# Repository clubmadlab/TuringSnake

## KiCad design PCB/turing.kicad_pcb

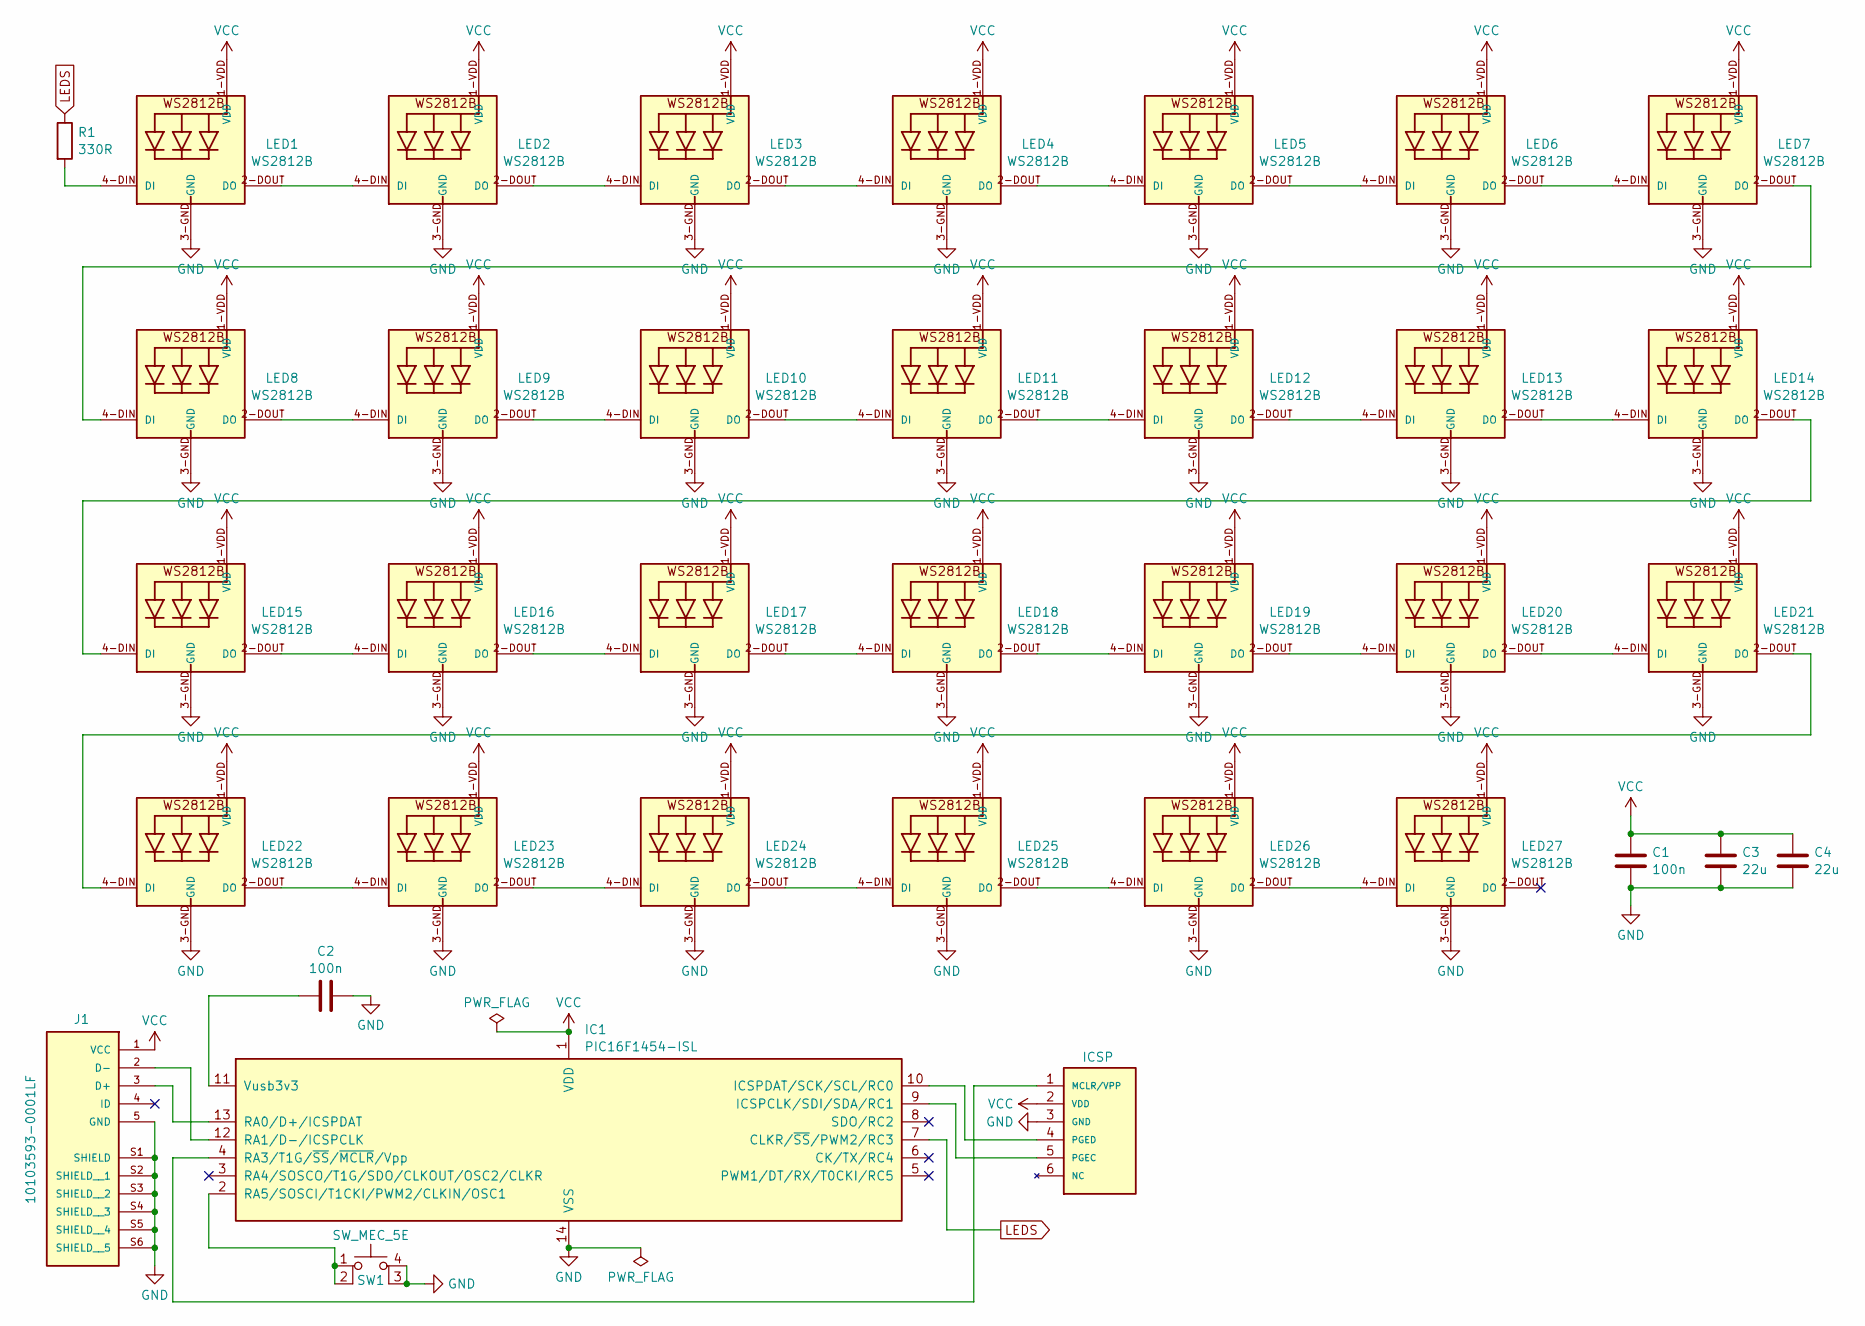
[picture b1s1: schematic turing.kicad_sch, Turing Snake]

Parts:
C1, C2: 100n; C_1206
C3, C4: 22u; C_1206
IC1: PIC16F1454-ISL; SOIC14
ICSP1: ICSP
J1: 10103593-0001LF; AMPHENOL_10103593-0001LF
LED1, LED2, LED3, LED4, LED5, LED6, LED7, LED8, LED9, LED10, LED11, LED12, LED13, LED14, LED15, LED16, LED17, LED18, LED19, LED20, LED21, LED22, LED23, LED24, LED25, LED26, LED27: WS2812B
R1: 330R; R_1206
SW1: SW_MEC_5E; pushbutton_min_tactile_SMD

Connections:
GND: C1.2, C2.1, C3.2, C4.2, IC1.14 (VSS), ICSP1.3 (GND), J1.5 (GND), J1.S1 (SHIELD), J1.S2 (SHIELD__1), J1.S3 (SHIELD__2), J1.S4 (SHIELD__3), J1.S5 (SHIELD__4), J1.S6 (SHIELD__5), LED1.3-GND (GND), LED2.3-GND (GND), LED3.3-GND (GND), LED4.3-GND (GND), LED5.3-GND (GND), LED6.3-GND (GND), LED7.3-GND (GND), LED8.3-GND (GND), LED9.3-GND (GND), LED10.3-GND (GND), LED11.3-GND (GND), LED12.3-GND (GND), LED13.3-GND (GND), LED14.3-GND (GND), LED15.3-GND (GND), LED16.3-GND (GND), LED17.3-GND (GND), LED18.3-GND (GND), LED19.3-GND (GND), LED20.3-GND (GND), LED21.3-GND (GND), LED22.3-GND (GND), LED23.3-GND (GND), LED24.3-GND (GND), LED25.3-GND (GND), LED26.3-GND (GND), LED27.3-GND (GND), SW1.3 (K), SW1.4 (A)
LEDS: IC1.7 (CLKR/~SS/PWM2/RC3), R1.1
unnamed: IC1.9 (ICSPCLK/SDI/SDA/RC1), ICSP1.5 (PGEC)
unnamed: IC1.10 (ICSPDAT/SCK/SCL/RC0), ICSP1.4 (PGED)
unnamed: IC1.13 (RA0/D+/ICSPDAT), J1.3 (D+)
unnamed: IC1.12 (RA1/D-/ICSPCLK), J1.2 (D-)
unnamed: IC1.4 (RA3/T1G/~SS/~MCLR/Vpp), ICSP1.1 (MCLR/VPP)
unnamed: IC1.2 (RA5/SOSCI/T1CKI/PWM2/CLKIN/OSC1), SW1.1, SW1.2
unnamed: C2.2, IC1.11 (Vusb3v3)
unnamed: LED1.4-DIN (DI), R1.2
unnamed: LED1.2-DOUT (DO), LED2.4-DIN (DI)
unnamed: LED2.2-DOUT (DO), LED3.4-DIN (DI)
unnamed: LED3.2-DOUT (DO), LED4.4-DIN (DI)
unnamed: LED4.2-DOUT (DO), LED5.4-DIN (DI)
unnamed: LED5.2-DOUT (DO), LED6.4-DIN (DI)
unnamed: LED6.2-DOUT (DO), LED7.4-DIN (DI)
unnamed: LED7.2-DOUT (DO), LED8.4-DIN (DI)
unnamed: LED8.2-DOUT (DO), LED9.4-DIN (DI)
unnamed: LED9.2-DOUT (DO), LED10.4-DIN (DI)
unnamed: LED10.2-DOUT (DO), LED11.4-DIN (DI)
unnamed: LED11.2-DOUT (DO), LED12.4-DIN (DI)
unnamed: LED12.2-DOUT (DO), LED13.4-DIN (DI)
unnamed: LED13.2-DOUT (DO), LED14.4-DIN (DI)
unnamed: LED14.2-DOUT (DO), LED15.4-DIN (DI)
unnamed: LED15.2-DOUT (DO), LED16.4-DIN (DI)
unnamed: LED16.2-DOUT (DO), LED17.4-DIN (DI)
unnamed: LED17.2-DOUT (DO), LED18.4-DIN (DI)
unnamed: LED18.2-DOUT (DO), LED19.4-DIN (DI)
unnamed: LED19.2-DOUT (DO), LED20.4-DIN (DI)
unnamed: LED20.2-DOUT (DO), LED21.4-DIN (DI)
unnamed: LED21.2-DOUT (DO), LED22.4-DIN (DI)
unnamed: LED22.2-DOUT (DO), LED23.4-DIN (DI)
unnamed: LED23.2-DOUT (DO), LED24.4-DIN (DI)
unnamed: LED24.2-DOUT (DO), LED25.4-DIN (DI)
unnamed: LED25.2-DOUT (DO), LED26.4-DIN (DI)
unnamed: LED26.2-DOUT (DO), LED27.4-DIN (DI)
VCC: C1.1, C3.1, C4.1, IC1.1 (VDD), ICSP1.2 (VDD), J1.1 (VCC), LED1.1-VDD (VDD), LED2.1-VDD (VDD), LED3.1-VDD (VDD), LED4.1-VDD (VDD), LED5.1-VDD (VDD), LED6.1-VDD (VDD), LED7.1-VDD (VDD), LED8.1-VDD (VDD), LED9.1-VDD (VDD), LED10.1-VDD (VDD), LED11.1-VDD (VDD), LED12.1-VDD (VDD), LED13.1-VDD (VDD), LED14.1-VDD (VDD), LED15.1-VDD (VDD), LED16.1-VDD (VDD), LED17.1-VDD (VDD), LED18.1-VDD (VDD), LED19.1-VDD (VDD), LED20.1-VDD (VDD), LED21.1-VDD (VDD), LED22.1-VDD (VDD), LED23.1-VDD (VDD), LED24.1-VDD (VDD), LED25.1-VDD (VDD), LED26.1-VDD (VDD), LED27.1-VDD (VDD)

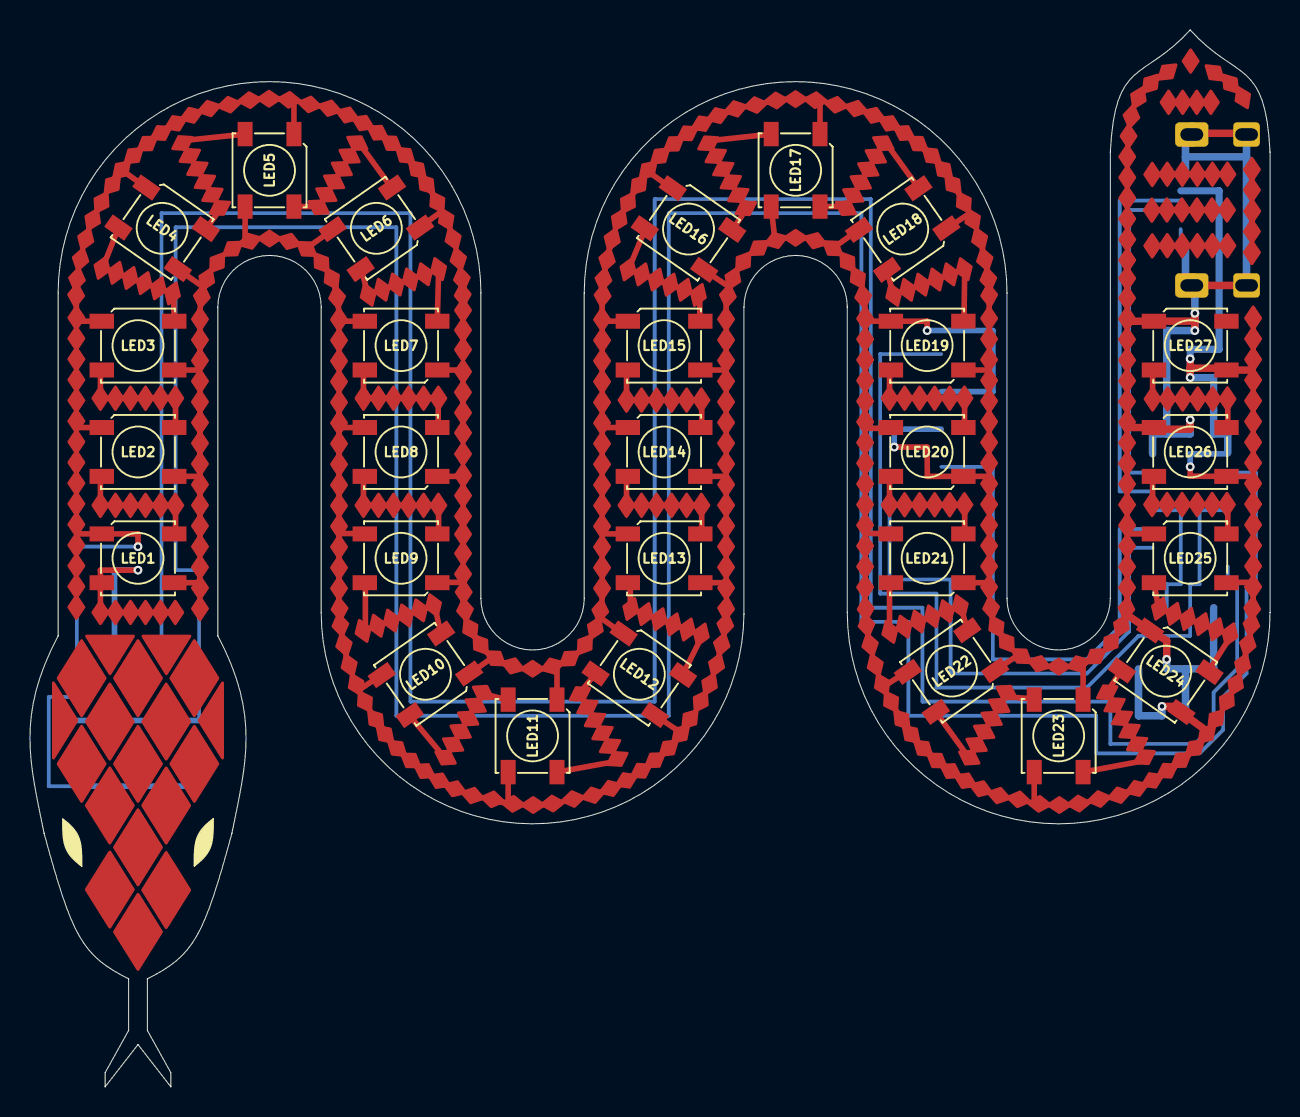
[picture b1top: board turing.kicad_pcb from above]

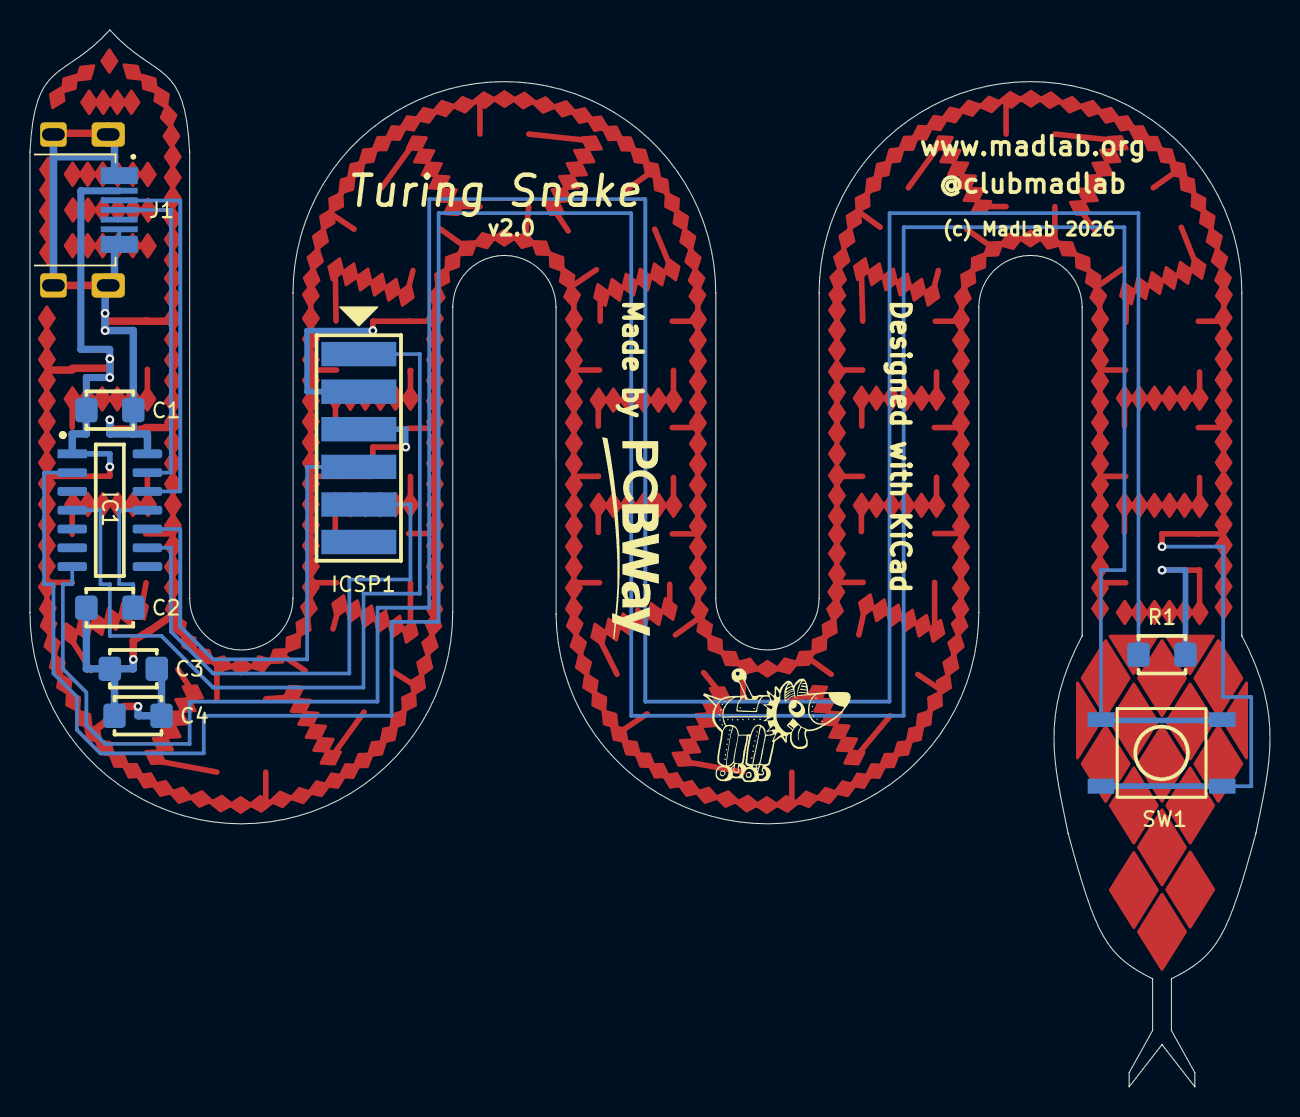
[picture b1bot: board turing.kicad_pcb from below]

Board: 2 copper layers, 83.8 x 71.4 mm, 36 parts (9 on the bottom side), 37 nets.
